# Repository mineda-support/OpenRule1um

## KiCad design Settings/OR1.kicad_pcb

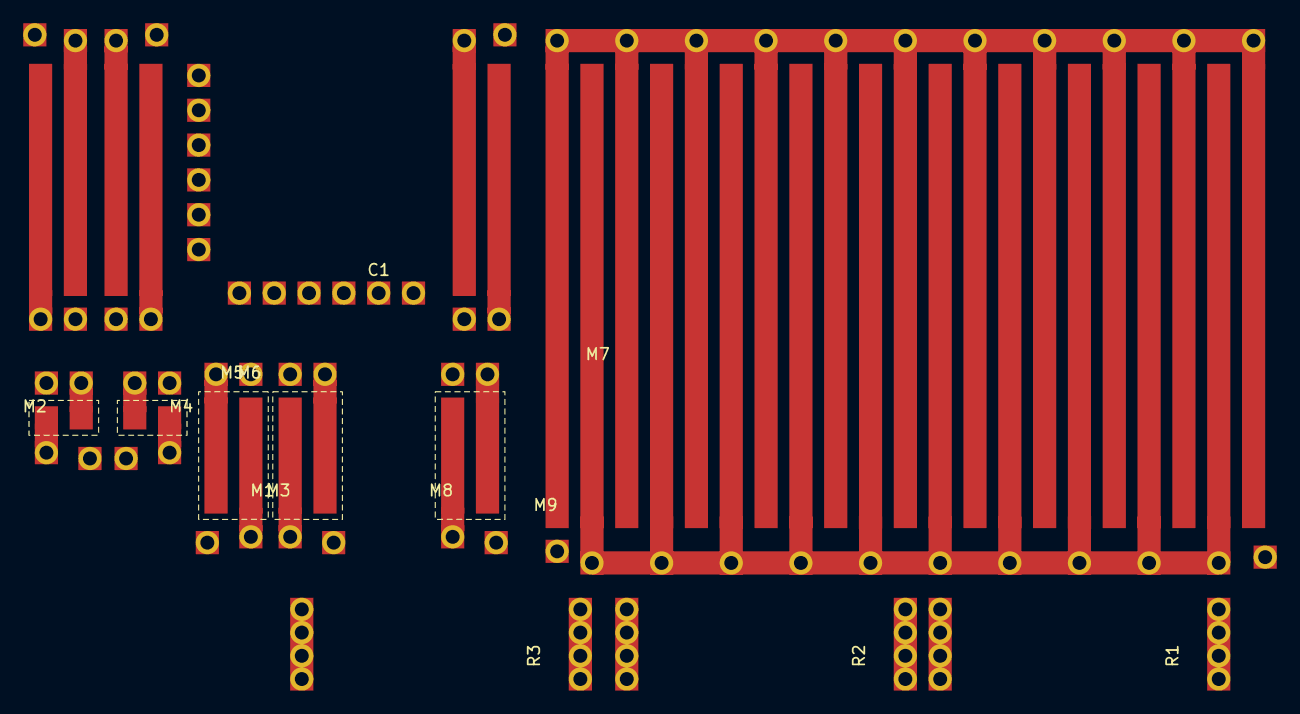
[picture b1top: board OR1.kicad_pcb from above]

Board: 2 copper layers, 13 parts (0 on the bottom side), 10 nets, no tracks yet.

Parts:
C1: OpenRule1um_v2#Pdiff_cap.l19w18.5m0
M1: OpenRule1um_v2#Nch.l1w10.0m1_0111110_MY
M2: OpenRule1um_v2#Nch.l1w1.2m1_0111110
M3, M8: OpenRule1um_v2#Nch.l1w10.0m1_0111110
M4: OpenRule1um_v2#Nch.l1w1.2m1_0111110_MY
M5: OpenRule1um_v2#Pch.l1w20.0m1_0111110_MY
M6, M7: OpenRule1um_v2#Pch.l1w20.0m1_0111110
M9: OpenRule1um_v2#Pch.l1w40.0m20_0111110
R1, R2, R3: OpenRule1um_v2#HR_poly.l20w8m1

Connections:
/Ibias: M1.1 (D), M1.2 (G), M3.2 (G), M8.2 (G)
/Vdd: M5.3 (S), M5.4 (B), M6.3 (S), M6.4 (B), M7.3 (S), M7.4 (B), M9.3 (S), M9.4 (B)
/Vout: M4.2 (G), R1.2 (MINUS), R2.1 (PLUS)
/Vreg: M9.1 (D), R1.1 (PLUS)
/Vss: M1.3 (S), M1.4 (B), M2.4 (B), M3.3 (S), M3.4 (B), M4.4 (B), M8.3 (S), M8.4 (B), R3.2 (MINUS)
unnamed: C1.2 (MINUS), M4.1 (D), M6.1 (D), M7.2 (G)
unnamed: C1.1 (PLUS), M7.1 (D), M8.1 (D), M9.2 (G)
unnamed: M2.1 (D), M5.1 (D), M5.2 (G), M6.2 (G)
unnamed: M2.3 (S), M3.1 (D), M4.3 (S)
unnamed: R2.2 (MINUS), R3.1 (PLUS)
